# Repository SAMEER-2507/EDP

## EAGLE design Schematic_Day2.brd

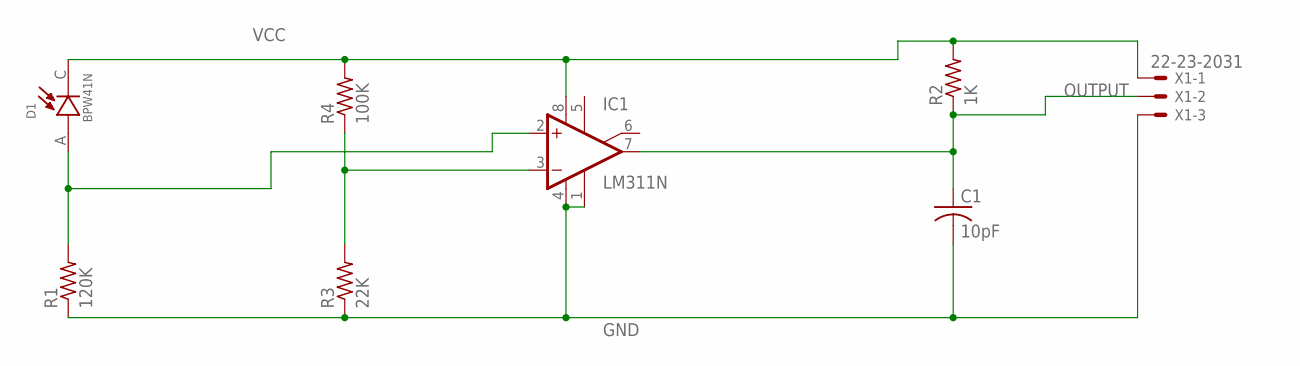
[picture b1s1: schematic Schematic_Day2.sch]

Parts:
C1: 10pF; C025-024X044
D1: BPW41N; DIO_BPW41N
IC1: LM311N; DIL08
R1: 120K; 0204/5
R2: 1K; 0204/5
R3: 22K; 0204/5
R4: 100K; 0204/5
X1: 22-23-2031

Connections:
GND: C1.2, IC1.1 (GND), IC1.4 (V-), R1.1, R3.1, X1.3
unnamed: D1.A, IC1.2 (+IN), R1.2
unnamed: IC1.3 (-IN), R3.2, R4.1
OUTPUT: C1.1, IC1.7 (OUT), R2.1, X1.2
VCC: D1.C, IC1.8 (V+), R2.2, R4.2, X1.1

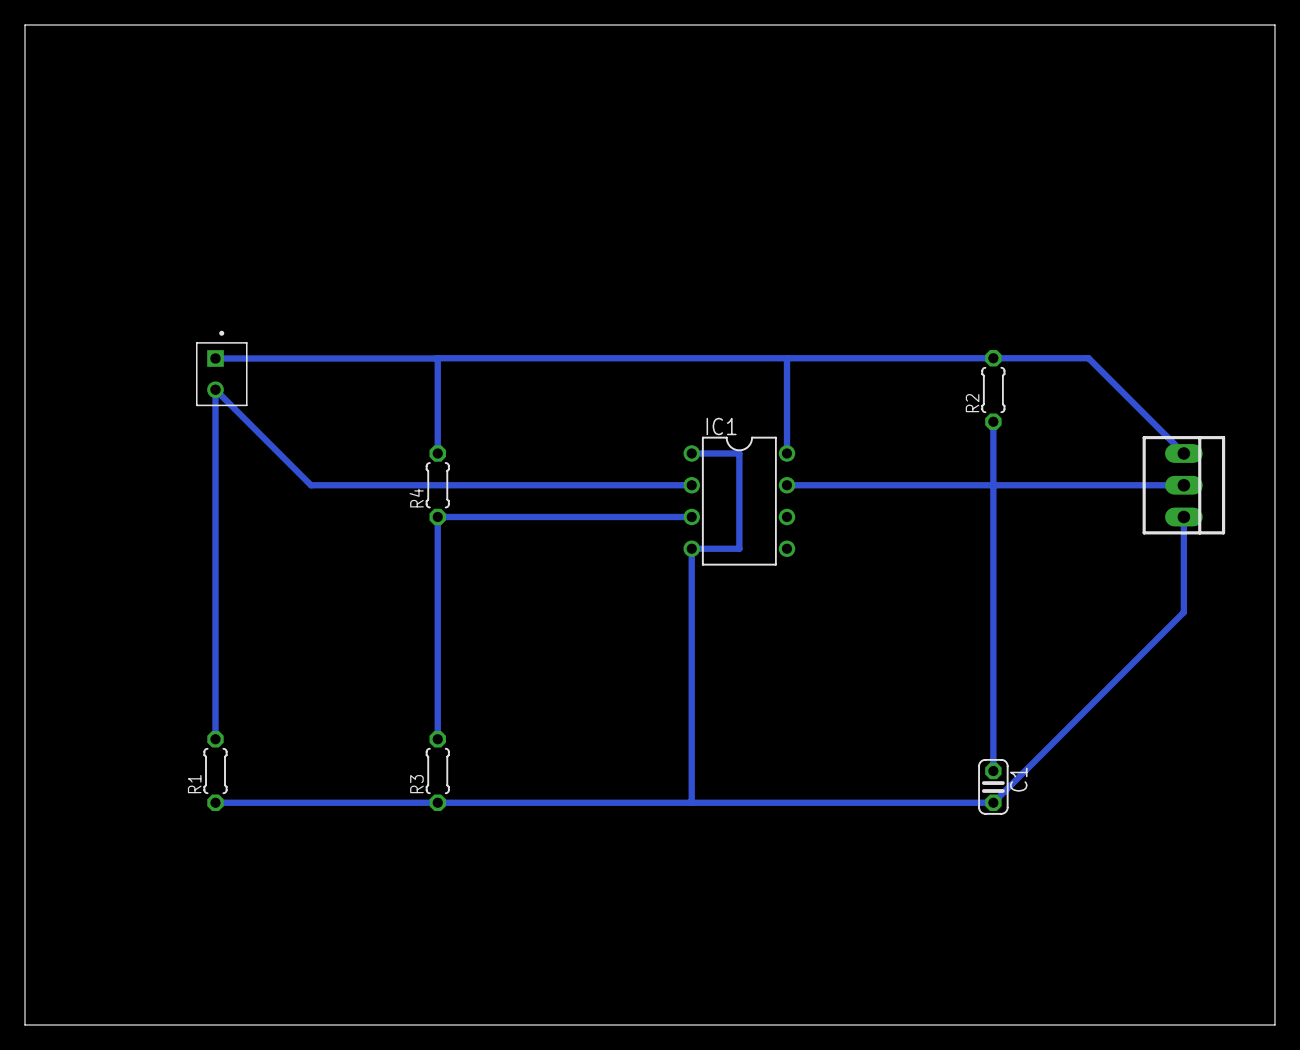
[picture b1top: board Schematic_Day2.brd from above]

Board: 2 copper layers, 100.0 x 80.0 mm, 8 parts (0 on the bottom side), 5 nets.

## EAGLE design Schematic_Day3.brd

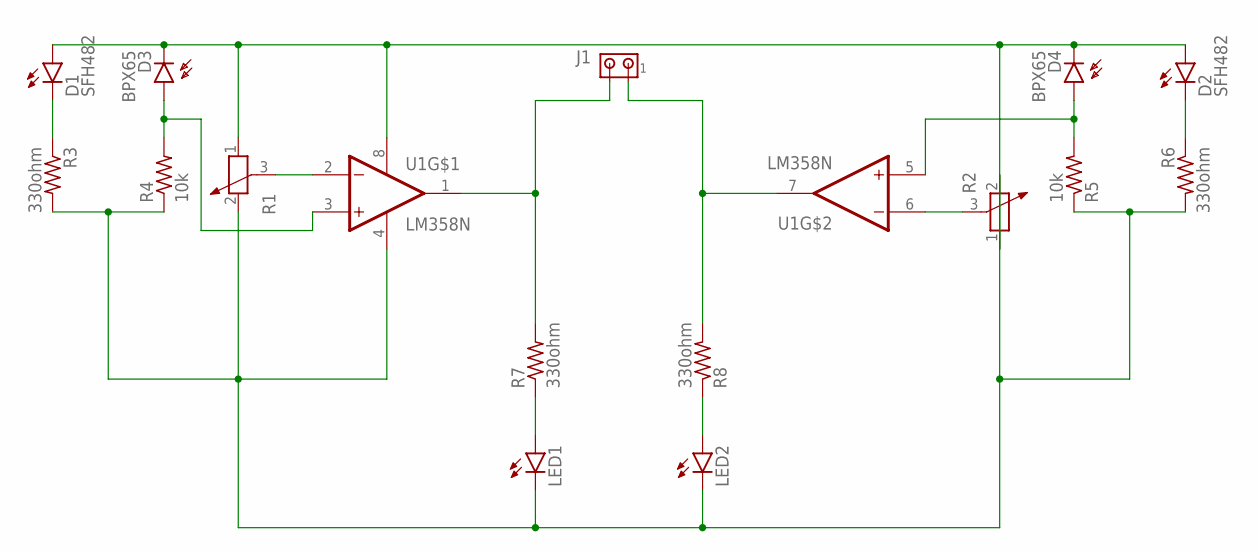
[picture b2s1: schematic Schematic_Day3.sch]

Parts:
D1, D2: SFH482
D3, D4: BPX65
J1: MTA02-100; 10X02MTA
LED1, LED2: LED3MM
R1, R2: POTENTIOMETER_PT-10; PT-10
R3, R6, R7, R8: 330ohm; 0204/5
R4, R5: 10k; 0204/5
U1: LM358N; DIP762W46P254L960H508Q8

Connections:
unnamed: D2.K (C), R6.1
unnamed: R2.3, U1.6 (2IN-)
unnamed: J1.1, R8.2, U1.7 (2OUT)
unnamed: LED2.A, R8.1
unnamed: D4.A, R5.2, U1.5 (2IN+)
unnamed: D1.K (C), R3.1
unnamed: LED1.K (C), LED2.K (C), R1.2, R2.2, R3.2, R4.1, R5.1, R6.2, U1.4 (GND)
unnamed: LED1.A, R7.1
unnamed: J1.2, R7.2, U1.1 (1OUT)
unnamed: D3.A, R4.2, U1.3 (1IN+)
unnamed: D1.A, D2.A, D3.K (C), D4.K (C), R1.1, R2.1, U1.8 (VCC)
unnamed: R1.3, U1.2 (1IN-)

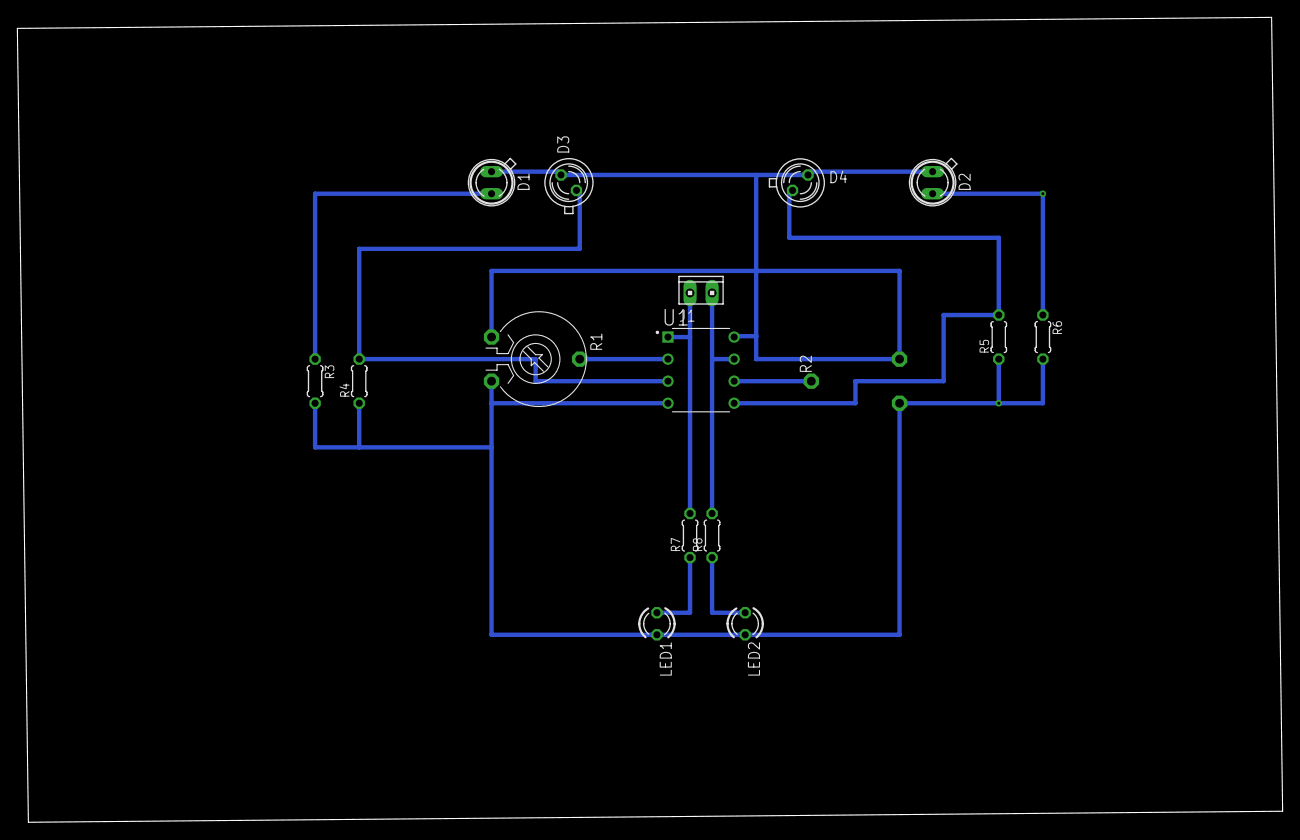
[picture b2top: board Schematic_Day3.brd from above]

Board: 2 copper layers, 145.7 x 92.7 mm, 16 parts (1 on the bottom side), 12 nets.

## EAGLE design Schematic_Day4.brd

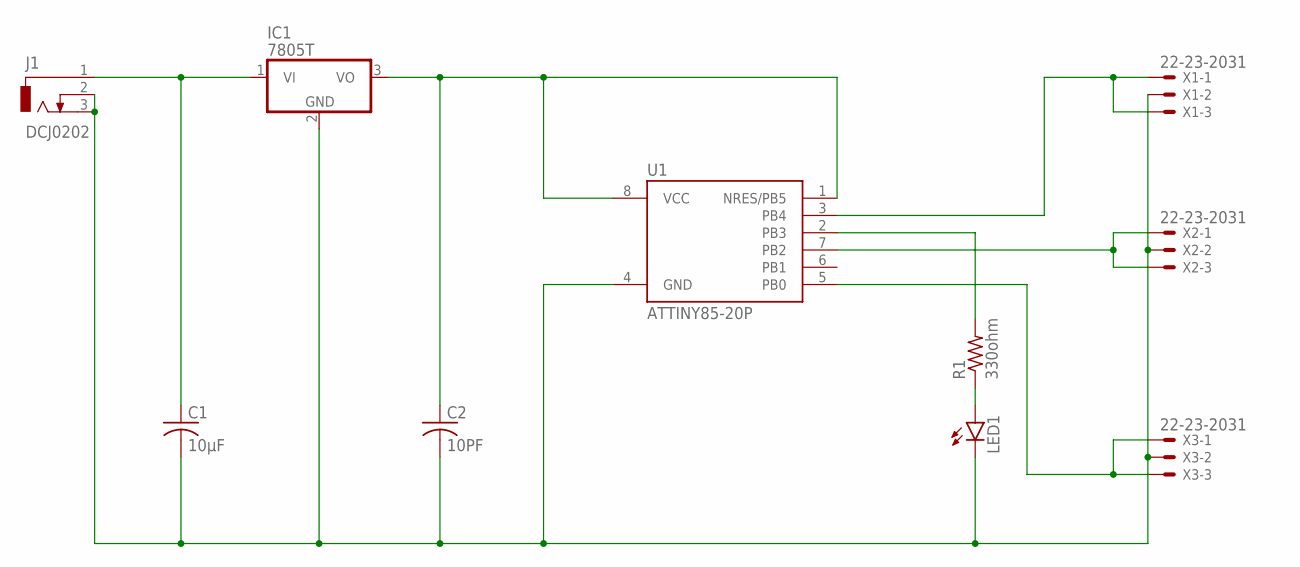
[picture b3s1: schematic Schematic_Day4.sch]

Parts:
C1: 10μF; C025-024X044
C2: 10PF; C025-024X044
IC1: 7805T; TO220H
J1: DCJ0202
LED1: LED3MM
R1: 330ohm; 0204/5
U1: ATTINY85-20P; PDIP08_300MIL
X1, X2, X3: 22-23-2031

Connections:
unnamed: C1.1, IC1.1 (VI), J1.1
unnamed: C1.2, C2.2, IC1.2 (GND), J1.2, J1.3, LED1.K (C), U1.3 (PB4), U1.4 (GND), U1.5 (PB0), U1.7 (PB2), X1.1, X1.2, X1.3, X2.1, X2.2, X2.3, X3.1, X3.2, X3.3
unnamed: C2.1, IC1.3 (VO), U1.1 (NRES/PB5), U1.8 (VCC)
unnamed: R1.2, U1.2 (PB3)
unnamed: LED1.A, R1.1

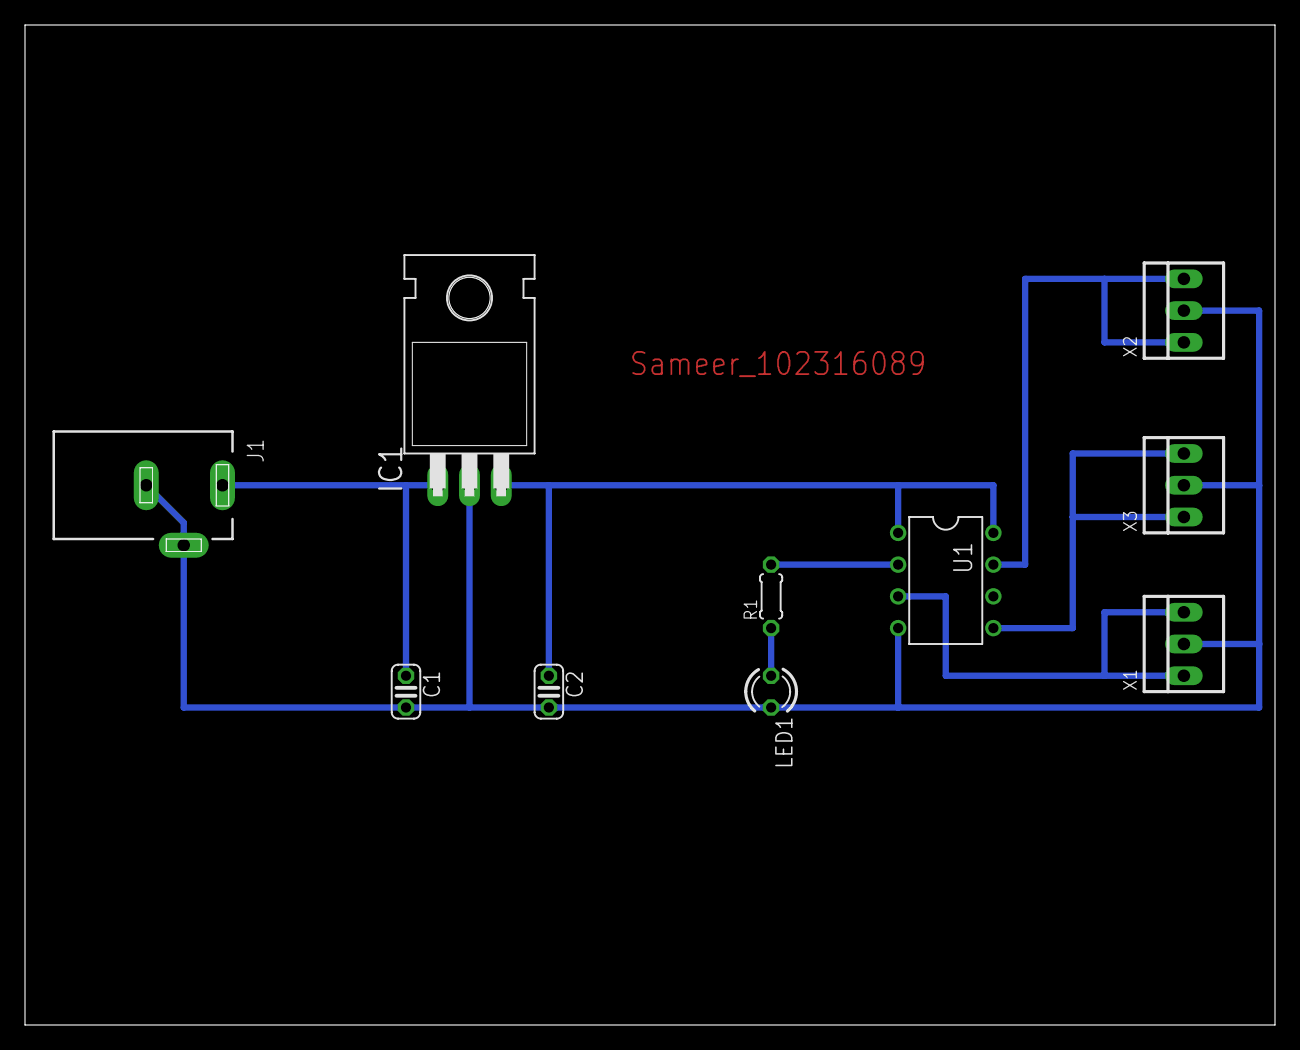
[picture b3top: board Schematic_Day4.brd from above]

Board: 2 copper layers, 100.0 x 80.0 mm, 10 parts (0 on the bottom side), 5 nets.

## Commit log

2025-08-02 nothing
